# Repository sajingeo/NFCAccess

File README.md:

NFCAccess
=========

Function: RFID/NFC entry

#### Usage:

#### Hardware:

### TODO
 - [ ] Hours of the Day access
 - [ ] Time allotted access
 - [ ] Different tones for different access/errors/holidays
 - [ ] LED light
 - [ ] Script to add cards
 - [ ] Button to auto-add card
 - [ ] Web interface
 - [ ] Mobile interface

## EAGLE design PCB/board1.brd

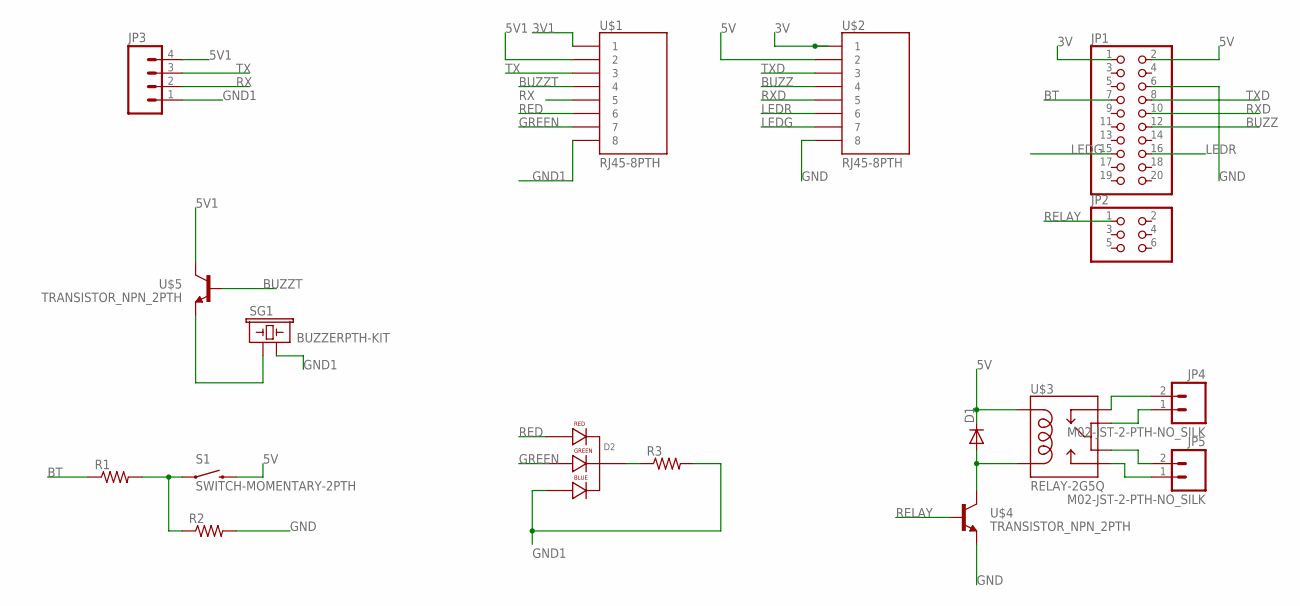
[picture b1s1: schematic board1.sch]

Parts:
D1: DIODEPTH; DIODE-1N4001
D2: LED-RGB-CC-THRUCLEAR; LED-RGB-THRU
JP1: PINHD-2X10; 2X10
JP2: PINHD-2X3; 2X03
JP3: M04PTH; 1X04
JP4, JP5: M02-JST-2-PTH-NO_SILK; JST-2-PTH-NS
R1, R2, R3: RESISTORPTH-1/4W; AXIAL-0.4
S1: SWITCH-MOMENTARY-2PTH; TACTILE-PTH
SG1: BUZZERPTH-KIT; BUZZER-12MM-KIT
U$1, U$2: RJ45-8PTH; RJ45-8
U$3: RELAY-2G5Q; RELAY-G5V
U$4, U$5: TRANSISTOR_NPN_2PTH; TO-92

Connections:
3V: JP1.1, U$2.1
3V1: U$1.1
5V: D1.C, JP1.2, S1.3 (2), U$2.2, U$3.2
5V1: JP3.4, U$1.2, U$5.1 (C)
BT: JP1.7, R1.P$1 (1)
BUZZ: JP1.12, U$2.4
BUZZT: U$1.4, U$5.2 (B)
GND: JP1.6, R2.P$2 (2), U$2.8, U$4.3 (E)
GND1: D2.4 (BLUE_CATHODE), JP3.1, R3.P$2 (2), SG1.- (2), U$1.8
GREEN: D2.3 (GREEN_CATHODE), U$1.7
LEDG: JP1.15, U$2.7
LEDR: JP1.16, U$2.6
unnamed: R1.P$2 (2), R2.P$1 (1), S1.1
unnamed: SG1.+ (1), U$5.3 (E)
unnamed: D1.A, U$3.9, U$4.1 (C)
unnamed: JP4.2, U$3.1
unnamed: JP4.1, U$3.5
unnamed: JP5.2, U$3.6
unnamed: JP5.1, U$3.10
unnamed: D2.2 (CATHODE), R3.P$1 (1)
RED: D2.1 (RED_CATHODE), U$1.6
RELAY: JP2.1, U$4.2 (B)
RX: JP3.2, U$1.5
RXD: JP1.10, U$2.5
TX: JP3.3, U$1.3
TXD: JP1.8, U$2.3

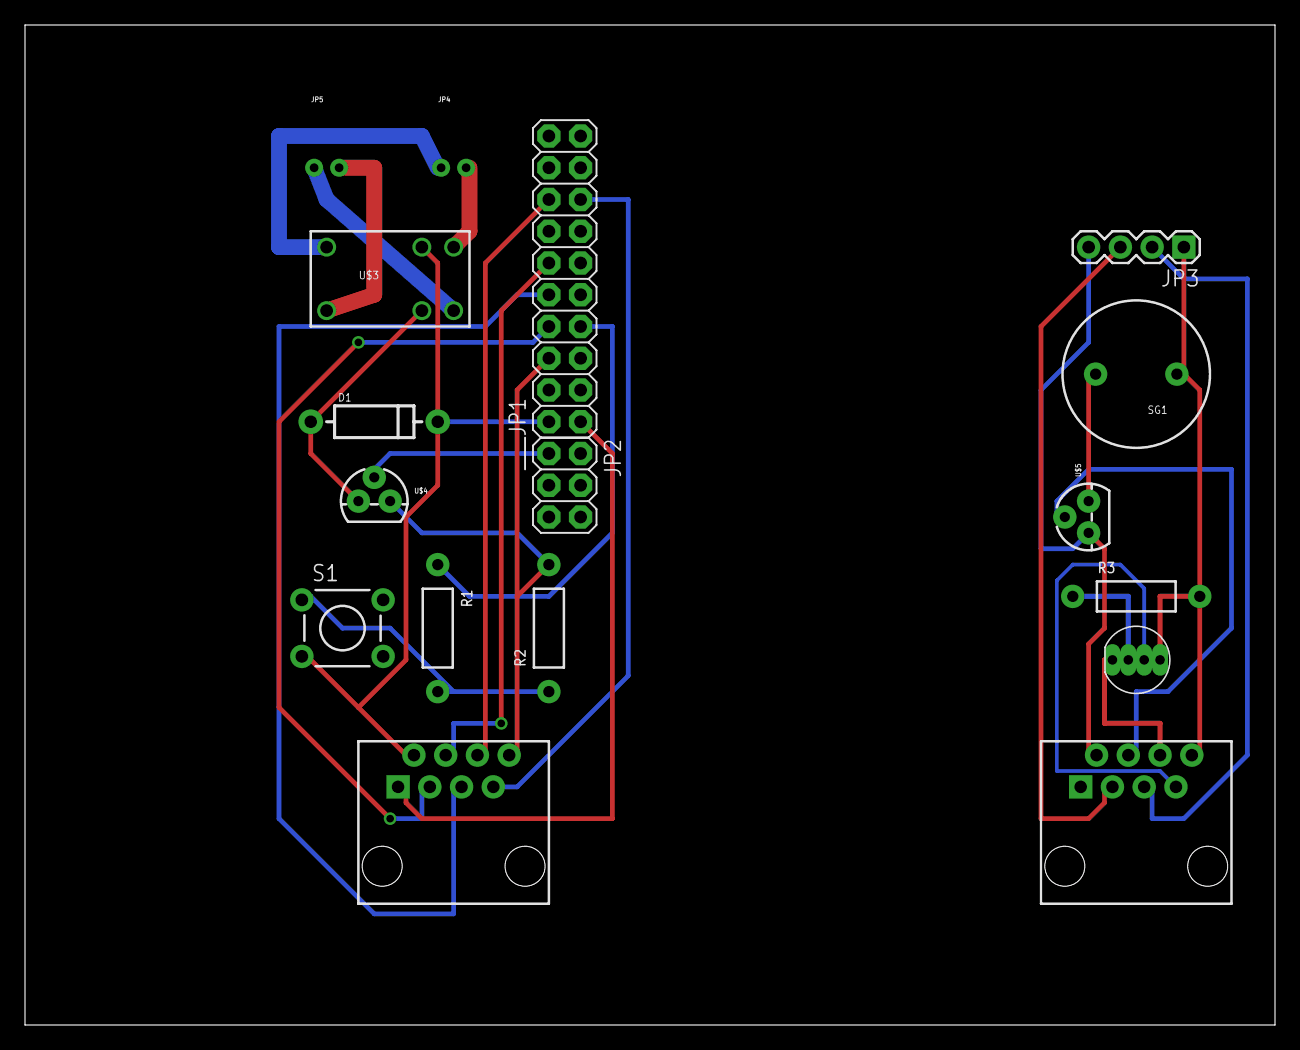
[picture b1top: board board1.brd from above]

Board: 2 copper layers, 100.0 x 80.0 mm, 17 parts (0 on the bottom side), 25 nets.

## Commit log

2013-11-15 formated README.md
2013-11-15 formated todo list in README.md
2014-01-22 added sms alert script
2014-01-23 added PCB files

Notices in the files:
parts and their libraries:
SparkFun-Connectors: Licensing: CC v3.0 Share-Alike You are welcome to use this library for commercial purposes.
